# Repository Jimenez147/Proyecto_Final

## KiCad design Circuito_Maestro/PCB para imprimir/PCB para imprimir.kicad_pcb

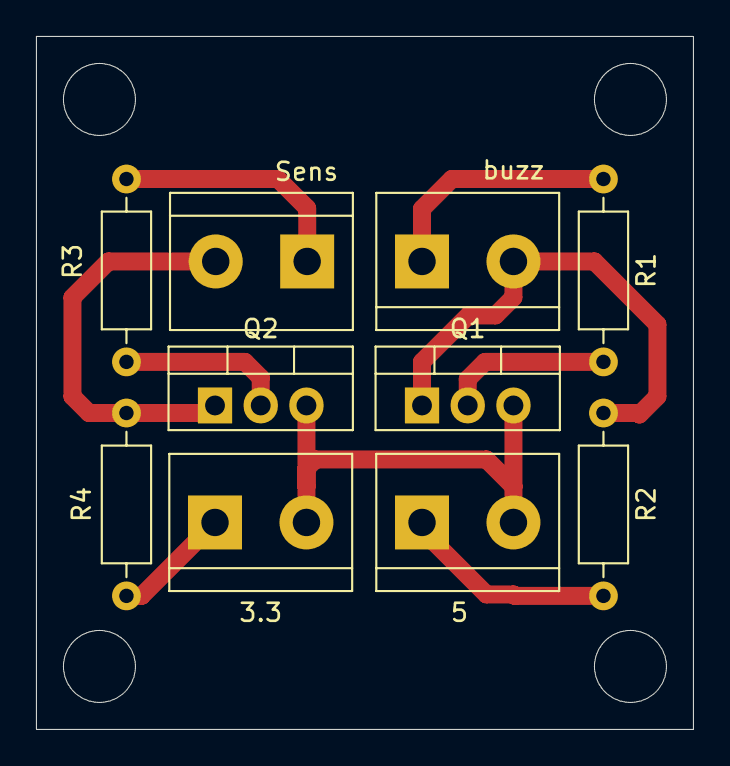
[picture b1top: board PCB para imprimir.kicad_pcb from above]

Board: 2 copper layers, 36.5 x 38.5 mm, 10 parts (0 on the bottom side), 9 nets.

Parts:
3.3, 5: Conn_01x02_Pin; TerminalBlock_bornier-2_P5.08mm
Q1, Q2: NMOS; TO-220-3_Vertical
R1, R2, R3, R4: R; R_Axial_DIN0207_L6.3mm_D2.5mm_P10.16mm_Horizontal
Sens: Conn_01x02_Pin; TerminalBlock_bornier-2_P5.08mm
buzz: Conn_01x02_Pin; TerminalBlock_bornier-2_P5.08mm

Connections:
+3.3V: 3.3.1, R4.2
+5V: 5.1, R2.2
/ESP_sens: Q2.1 (D), R4.1, Sens.2
/buzz: Q1.1 (D), R2.1, buzz.2
GND: 3.3.2, 5.2, Q1.3 (S), Q2.3 (S)
unnamed: R1.1, buzz.1
unnamed: Q1.2 (G), R1.2
unnamed: Q2.2 (G), R3.2
unnamed: R3.1, Sens.1

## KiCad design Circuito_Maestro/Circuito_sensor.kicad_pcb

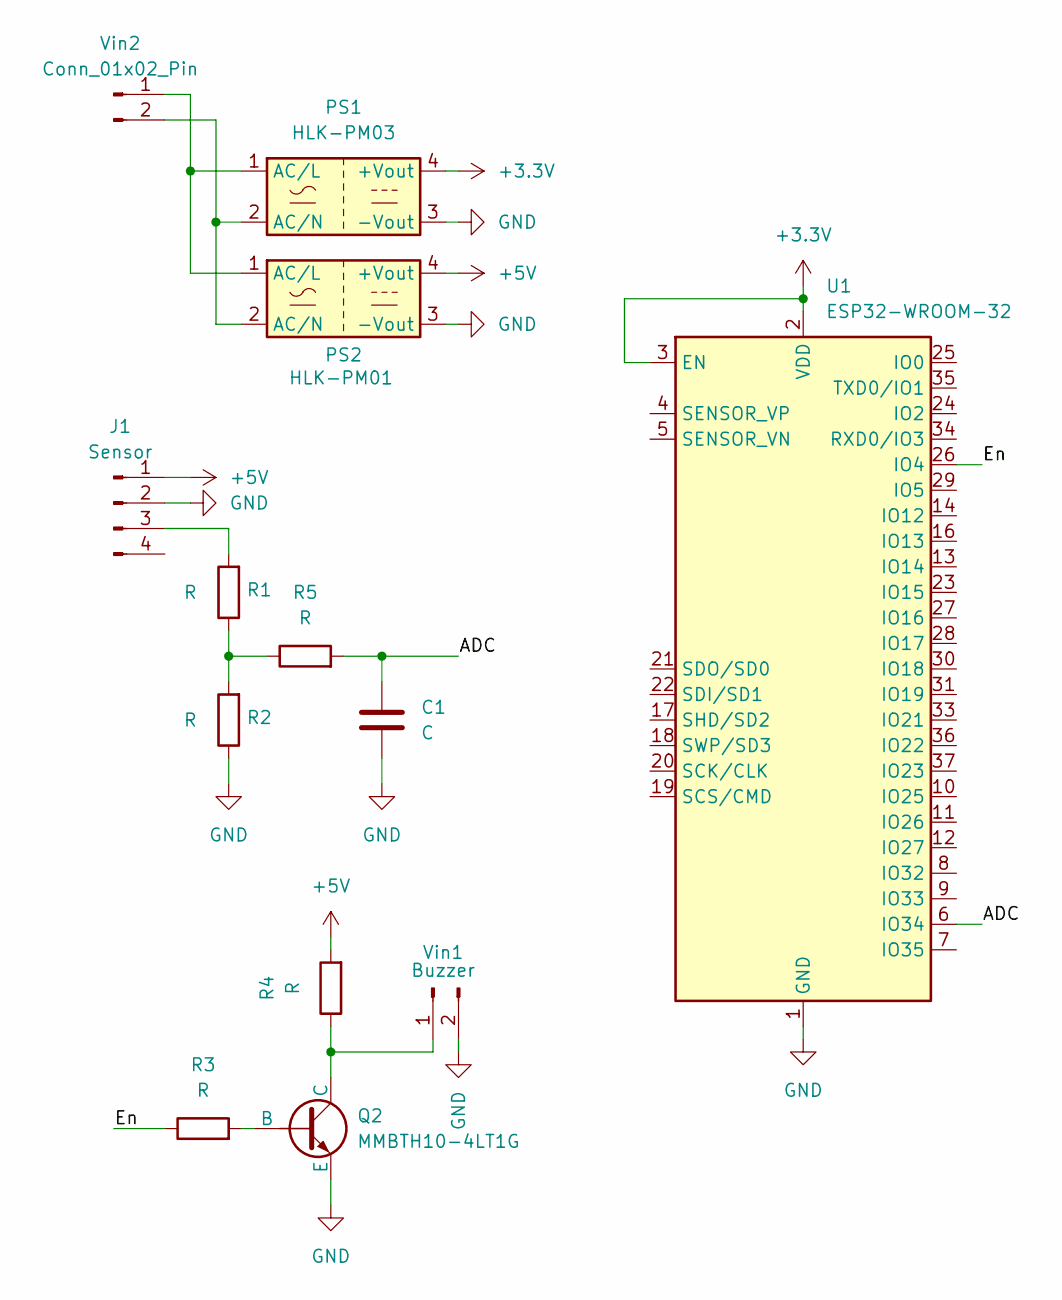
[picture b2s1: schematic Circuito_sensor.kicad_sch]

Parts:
C1: C; C_0201_0603Metric
J1: Sensor; PinHeader_1x04_P1.00mm_Vertical
PS1: HLK-PM03; Converter_ACDC_Hi-Link_HLK-PMxx
PS2: HLK-PM01; Converter_ACDC_Hi-Link_HLK-PMxx
Q2: MMBTH10-4LT1G; SOT-23-3
R1, R2, R3, R4, R5: R; R_0201_0603Metric
U1: ESP32-WROOM-32
Vin1: Buzzer; JST_PH_B2B-PH-K_1x02_P2.00mm_Vertical
Vin2: Conn_01x02_Pin; JST_PH_B2B-PH-K_1x02_P2.00mm_Vertical

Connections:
+3.3V: PS1.4 (+Vout), U1.2 (VDD), U1.3 (EN)
+5V: J1.1, PS2.4 (+Vout), R4.2
/ADC: C1.1, R5.2, U1.6 (IO34)
/En: R3.1, U1.26 (IO4)
GND: C1.2, J1.2, PS1.3 (-Vout), PS2.3 (-Vout), Q2.3 (E), R2.1, U1.1 (GND), U1.15 (GND), U1.38 (GND), U1.39 (GND), Vin1.2
unnamed: J1.3, R1.2
unnamed: PS1.1 (AC/L), PS2.1 (AC/L), Vin2.1
unnamed: PS1.2 (AC/N), PS2.2 (AC/N), Vin2.2
unnamed: Q2.2 (B), R3.2
unnamed: Q2.1 (C), R4.1, Vin1.1
unnamed: R1.1, R2.2, R5.1

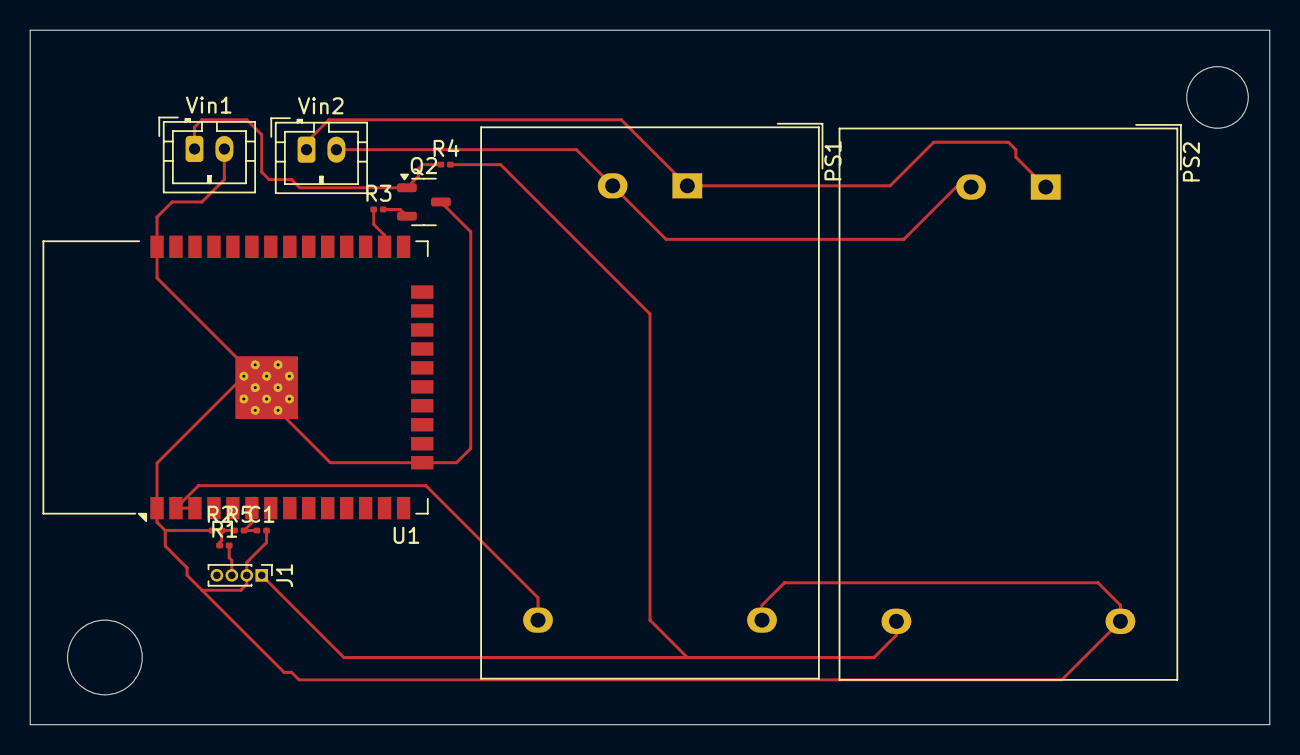
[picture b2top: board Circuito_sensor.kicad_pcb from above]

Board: 2 copper layers, 83.0 x 46.5 mm, 13 parts (0 on the bottom side), 11 nets.

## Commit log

2024-12-03 1st commit
2024-12-04 2nd commit
